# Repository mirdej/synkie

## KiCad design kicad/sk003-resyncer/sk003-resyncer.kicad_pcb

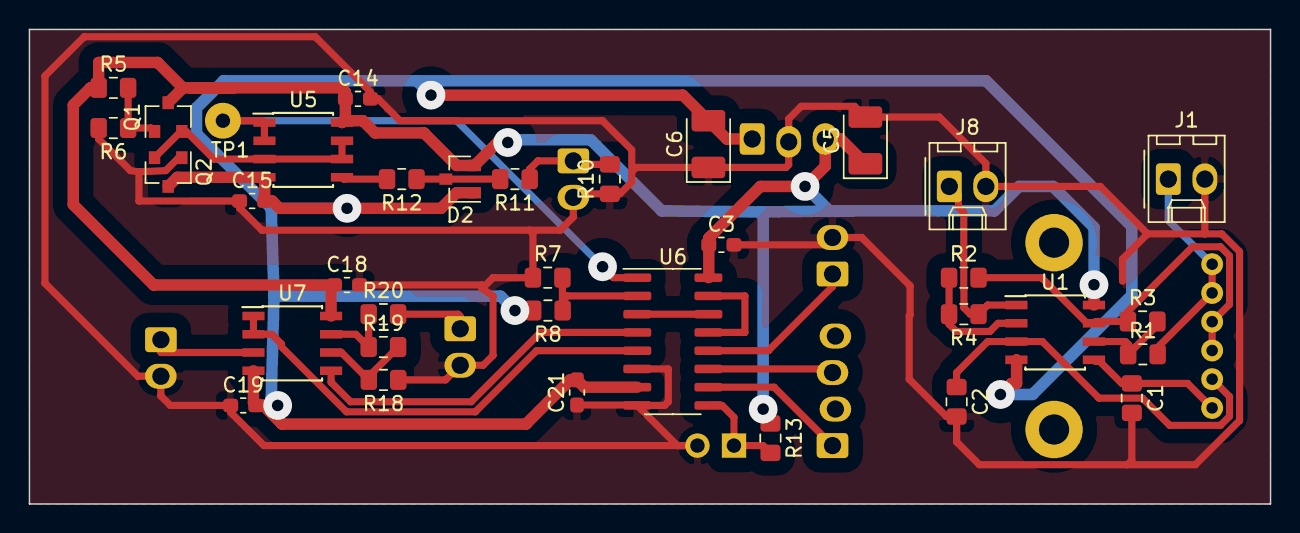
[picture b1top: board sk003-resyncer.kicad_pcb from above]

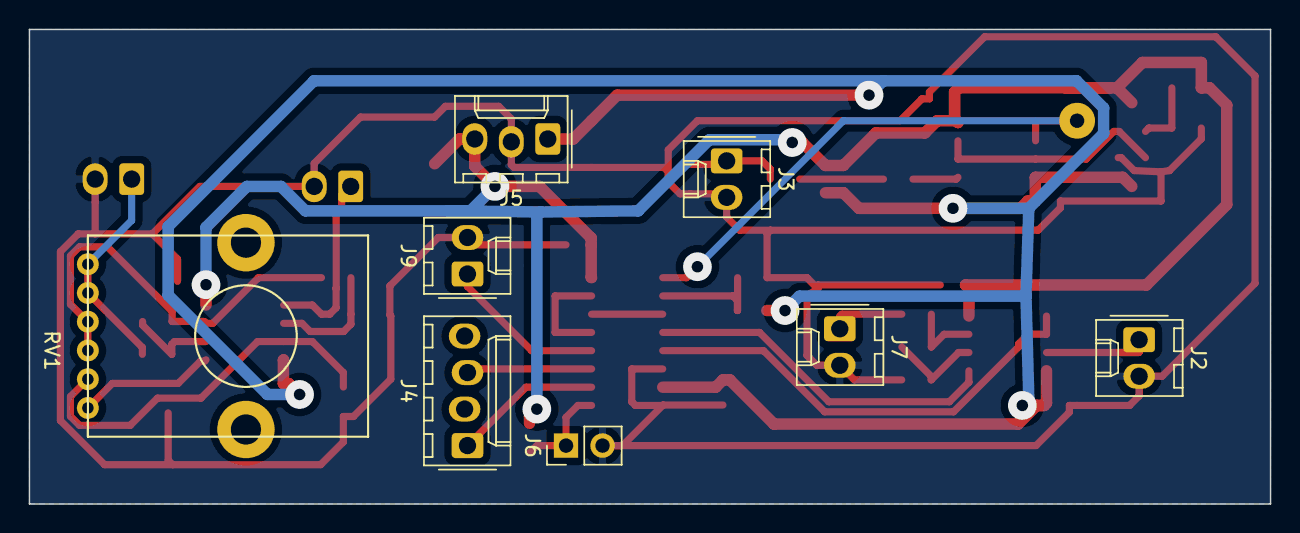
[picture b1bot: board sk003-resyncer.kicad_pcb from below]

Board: 2 copper layers, 86.4 x 33.0 mm, 43 parts (8 on the bottom side), 29 nets.

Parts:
C1, C2: 10p; C_0805_2012Metric_Pad1.15x1.40mm_HandSolder
C3, C14, C15, C18, C19, C21: 100n; C_0603_1608Metric_Pad1.05x0.95mm_HandSolder
C5, C6: 10u; CP_EIA-3528-21_Kemet-B_Pad1.50x2.35mm_HandSolder
D2: BAT54S; SOT-23
J1: BURST_IN; Molex_KK-254_AE-6410-02A_1x02_P2.54mm_Vertical
J2: GENLOCK; Molex_KK-254_AE-6410-02A_1x02_P2.54mm_Vertical
J3: SIFF_IN; Molex_KK-254_AE-6410-02A_1x02_P2.54mm_Vertical
J4: Conn_01x04; Molex_KK-254_AE-6410-04A_1x04_P2.54mm_Vertical
J5: Conn_01x03; Molex_KK-254_AE-6410-03A_1x03_P2.54mm_Vertical
J6: Switch; PinHeader_1x02_P2.54mm_Vertical
J7: VIDEO_OUT; Molex_KK-254_AE-6410-02A_1x02_P2.54mm_Vertical
J8: BURST_DELAYED; Molex_KK-254_AE-6410-02A_1x02_P2.54mm_Vertical
J9: Colorburst; Molex_KK-254_AE-6410-02A_1x02_P2.54mm_Vertical
Q1: Trans_NPN_Generic; SOT-23_BEC
Q2: Trans_PNP_Generic; SOT-23_BEC
R1, R2, R3, R4, R18, R19: 220; R_0805_2012Metric_Pad1.15x1.40mm_HandSolder
R5: 1k; R_0805_2012Metric_Pad1.15x1.40mm_HandSolder
R6: 150; R_0805_2012Metric_Pad1.15x1.40mm_HandSolder
R7: 300; R_0805_2012Metric_Pad1.15x1.40mm_HandSolder
R8, R13: 4k7; R_0805_2012Metric_Pad1.15x1.40mm_HandSolder
R10: 47k; R_0805_2012Metric_Pad1.15x1.40mm_HandSolder
R11, R12, R20: 75; R_0805_2012Metric_Pad1.15x1.40mm_HandSolder
RV1: R_POT_Dual; RK12L123
TP1: TestPoint; Solderpad_1mm
U1, U5, U7: LMH6643; SOIC-8_3.9x4.9mm_P1.27mm
U6: 4053; SOIC-16_3.9x9.9mm_P1.27mm

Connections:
+5V: C3.1, C5.1, C14.1, C18.1, D2.2, J5.3, Q1.C, R5.1, R13.1, U1.8, U5.8, U6.16, U7.8
-5V: C6.2, C15.2, C19.2, C21.2, D2.1, J5.1, Q2.C, R8.2, U1.4, U5.4, U6.7, U7.4
/clipper_out: TP1.1, U5.1, U5.2, U6.1
/colorburst: J9.1, U6.12
/hsync: J4.1, U6.10
/porch: J4.3, U6.11
/synctip: R7.2, R8.1, U6.2
GND: C1.2, C2.2, C3.2, C5.2, C6.1, C14.2, C15.1, C18.2, C19.1, C21.1, J1.2, J2.2, J3.2, J5.2, J6.2, J7.2, J8.2, J9.2, Q2.B, R6.2, R7.1, R10.1, R18.1, U6.6, U6.8
unnamed: C1.1, RV1.3, U1.5
unnamed: C2.1, RV1.6, U1.3
unnamed: D2.3, R11.2, R12.1
unnamed: J1.1, R1.2, RV1.1, RV1.2
unnamed: J2.1, U7.3
unnamed: J3.1, R10.2, R11.1
unnamed: J6.1, R13.2, U6.9
unnamed: J7.1, R20.2
unnamed: J8.1, R4.1, U1.1
unnamed: Q1.B, R5.2, R6.1
unnamed: Q1.E, Q2.E, U5.3, U5.6, U5.7
unnamed: R1.1, R3.2, U1.6
unnamed: R2.1, R4.2, U1.2
unnamed: R2.2, R3.1, RV1.4, RV1.5, U1.7
unnamed: R12.2, U5.5
unnamed: R18.2, R19.2, U7.6
unnamed: R19.1, R20.1, U7.7
unnamed: U6.4, U7.5
unnamed: U6.5, U7.1, U7.2
unnamed: U6.13, U6.15
unnamed: U6.3, U6.14

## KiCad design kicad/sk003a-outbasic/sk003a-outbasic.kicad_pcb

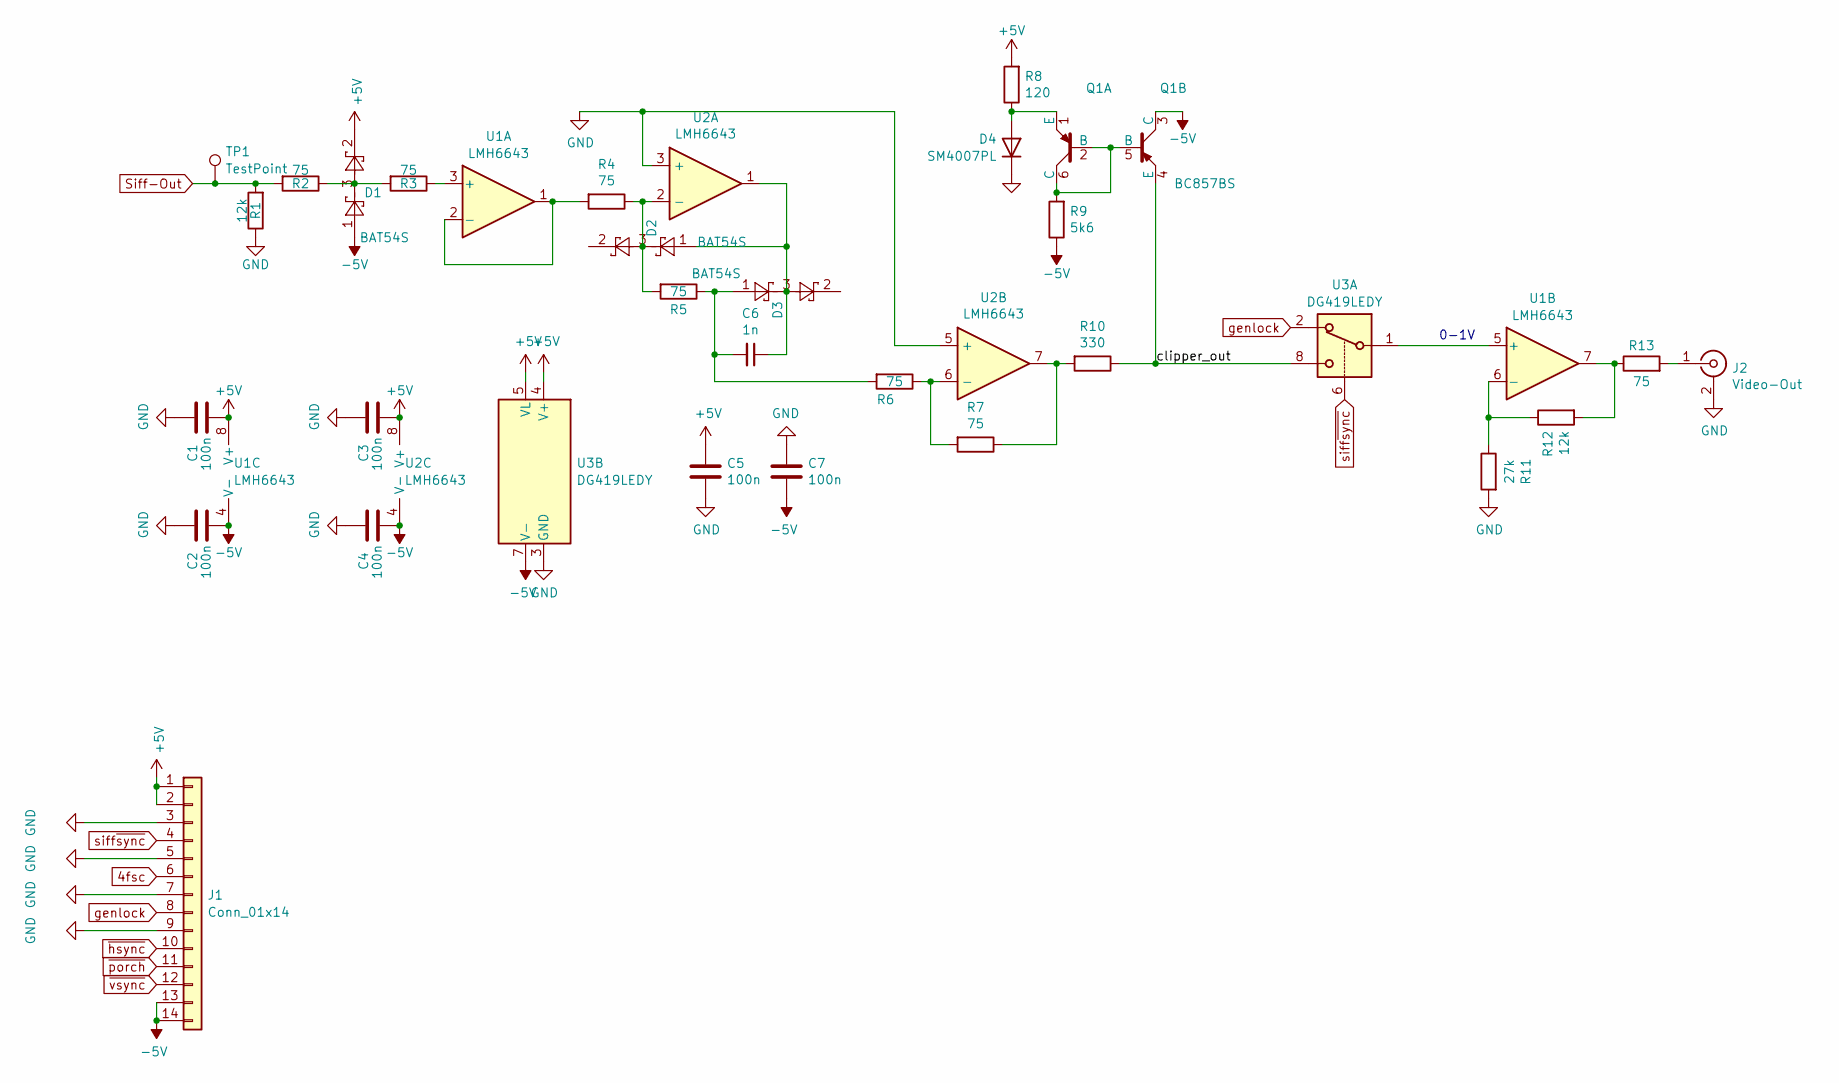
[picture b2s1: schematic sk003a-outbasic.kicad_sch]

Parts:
C1, C2, C3, C4, C5, C7: 100n; C_0603_1608Metric; LCSC C14663
C6: 1n; C_0603_1608Metric; LCSC C1588
D1, D2, D3: BAT54S; SOT-23; LCSC C7420333
D4: SM4007PL; D_SOD-123F; LCSC C64898
J1: Conn_01x14; SYNKIE-BUS.v3
J2: Video-Out; BNC_Aliexpress
Q1: BC857BS; SOT-363_SC-70-6_Handsoldering; LCSC C22381405
R1, R12: 12k; R_0603_1608Metric; LCSC C22790
R2, R3, R4, R5, R6, R7, R13: 75; R_0603_1608Metric; LCSC C4275
R8: 120; R_0603_1608Metric; LCSC C22787
R9: 5k6; R_0603_1608Metric; LCSC C23189
R10: 330; R_0603_1608Metric; LCSC C23138
R11: 27k; R_0603_1608Metric; LCSC C22967
TP1: TestPoint; TestPoint_THTPad_D4.0mm_Drill2.0mm
U1, U2: LMH6643; VSSOP-8_3x3mm_P0.65mm; LCSC C478382
U3: DG419LEDY; SOIC-8_3.9x4.9mm_P1.27mm; LCSC C2673265

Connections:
4fsc: J1.6
+5V: C1.2, C3.2, C5.1, D1.2, J1.1, J1.2, R8.2, U1.8 (V+), U2.8 (V+), U3.4 (V+), U3.5 (VL)
-5V: C2.2, C4.2, C7.2, D1.1, J1.13, J1.14, Q1.3 (C), R9.1, U1.4 (V-), U2.4 (V-), U3.7 (V-)
/clipper_out: Q1.4 (E), R10.1, U3.8
GND: C1.1, C2.1, C3.1, C4.1, C5.2, C7.1, D4.1 (K), J1.3, J1.5, J1.7, J1.9, J2.2 (Ext), R1.1, R11.2, U2.3 (+), U2.5 (+), U3.3 (GND)
unnamed: C6.1, D2.1, D3.3, U2.1
unnamed: C6.2, D3.1, R5.1, R6.2
unnamed: D1.3, R2.1, R3.2
unnamed: D4.2 (A), Q1.1 (E), R8.1
unnamed: J2.1 (In), R13.2
unnamed: Q1.2 (B), Q1.5 (B), Q1.6 (C), R9.2
unnamed: R7.1, R10.2, U2.7
unnamed: R12.2, R13.1, U1.7
unnamed: R3.1, U1.3 (+)
unnamed: R4.2, U1.1, U1.2 (-)
unnamed: U1.5 (+), U3.1
unnamed: R11.1, R12.1, U1.6 (-)
unnamed: D2.3, R4.1, R5.2, U2.2 (-)
unnamed: R6.1, R7.2, U2.6 (-)
Siff-Out: R1.2, R2.2, TP1.1 (1_1)
genlock: J1.8, U3.2
siff~sync: J1.4, U3.6
~hsync: J1.10
~porch: J1.11
~vsync: J1.12

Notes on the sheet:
0-1V

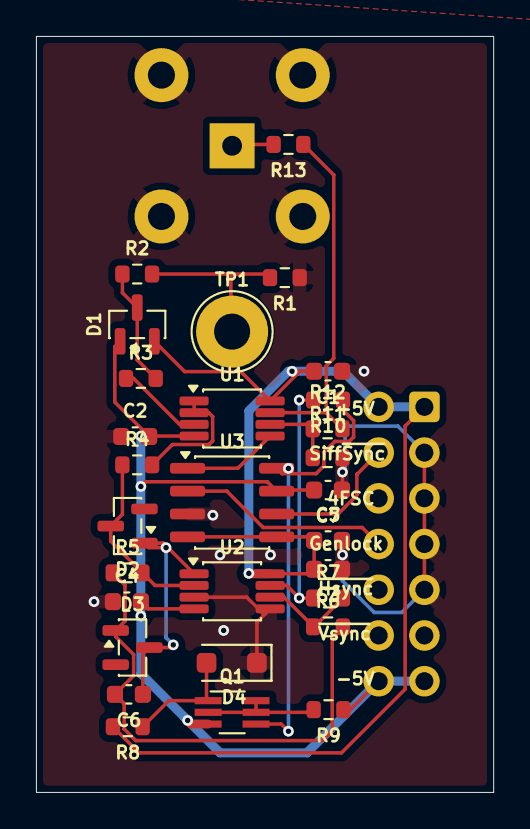
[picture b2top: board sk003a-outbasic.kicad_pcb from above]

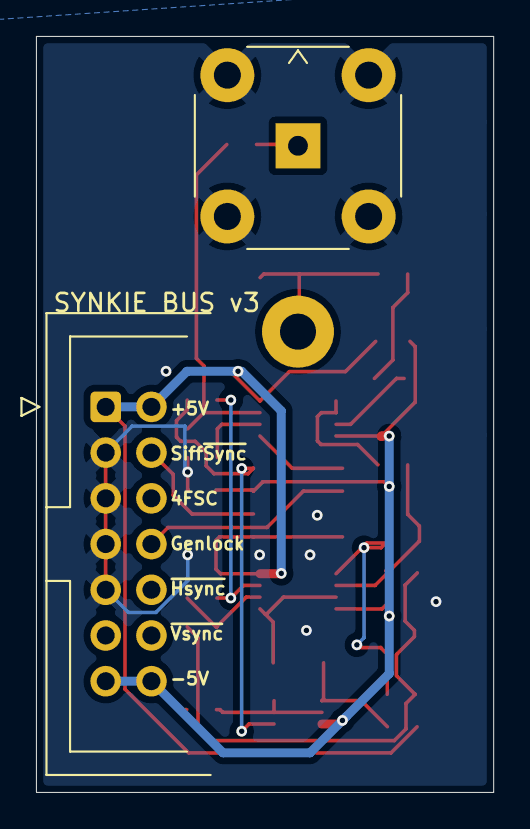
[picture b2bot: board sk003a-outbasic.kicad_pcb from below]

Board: 2 copper layers, 25.4 x 42.0 mm, 31 parts (2 on the bottom side), 21 nets.

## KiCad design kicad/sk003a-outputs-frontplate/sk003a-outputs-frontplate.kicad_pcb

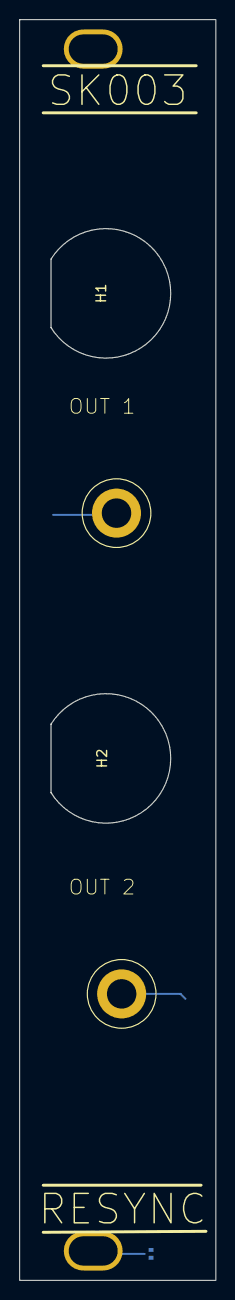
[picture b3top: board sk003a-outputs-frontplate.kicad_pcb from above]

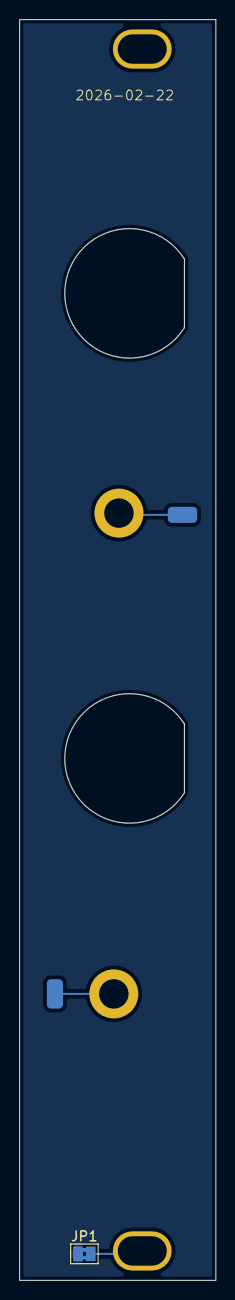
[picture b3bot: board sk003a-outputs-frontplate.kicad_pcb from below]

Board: 2 copper layers, 20.0 x 128.5 mm, 8 parts (3 on the bottom side), 3 nets.

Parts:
H1, H2: BNC; MolexBNCFrontpanel
J6: Out1; Banana2mm-Löthülse
J7: OUT; Banana2mm-Löthülse
J8, J9: Conn_01x01_Socket; smd-1pin
JP1: Jumper_2_Bridged; SolderJumper-2_P1.3mm_Bridged2Bar_Pad1.0x1.5mm
N1: Housing; Frontplate_20mm

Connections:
unnamed: J6.1 (Pin_1_1), J9.1 (Pin_1_1)
unnamed: J7.1 (Pin_1_1), J8.1 (Pin_1_1)
unnamed: JP1.2 (B), N1.1 (PAD_1)

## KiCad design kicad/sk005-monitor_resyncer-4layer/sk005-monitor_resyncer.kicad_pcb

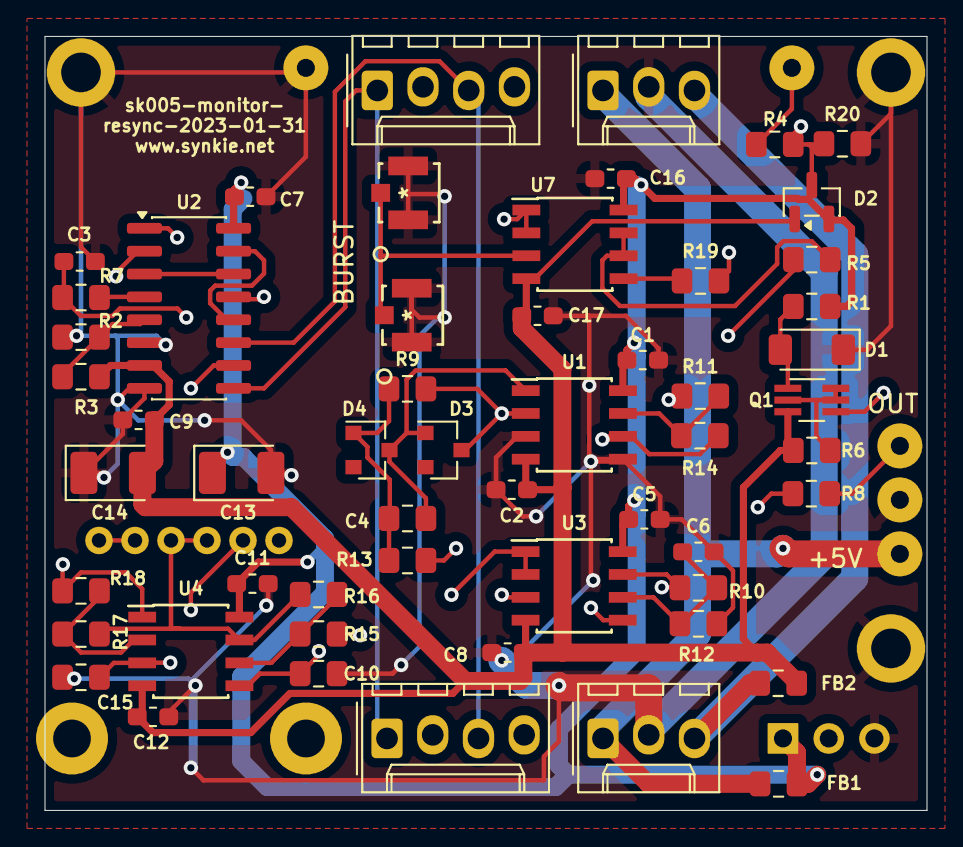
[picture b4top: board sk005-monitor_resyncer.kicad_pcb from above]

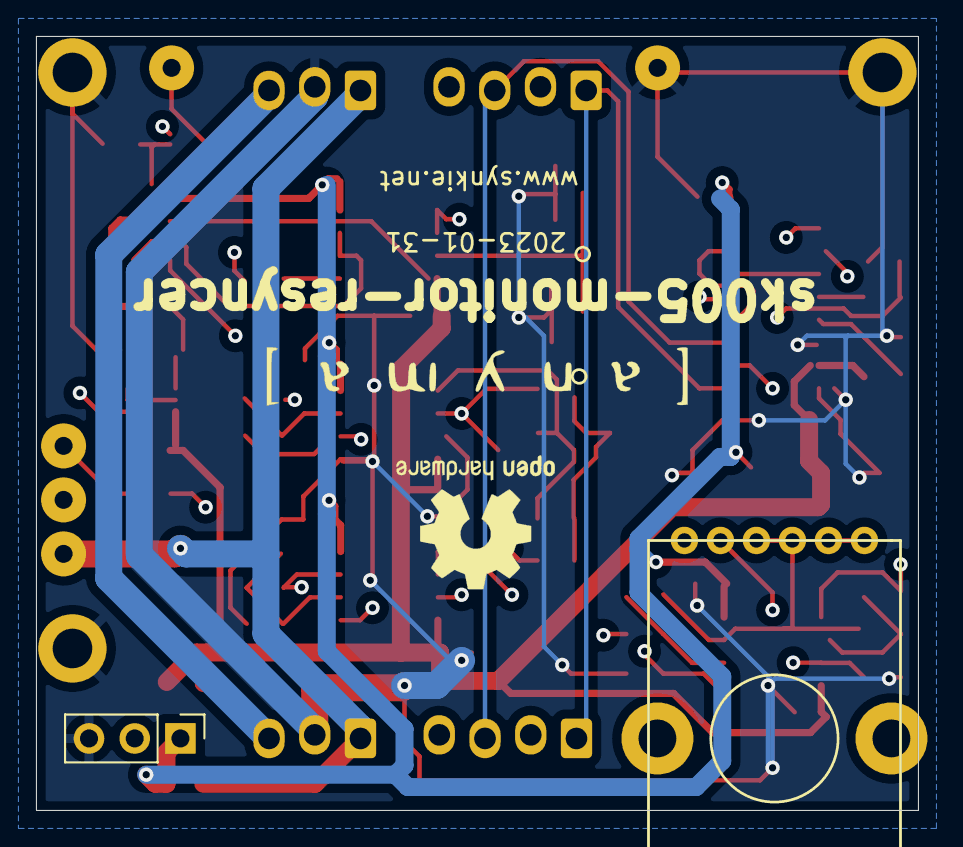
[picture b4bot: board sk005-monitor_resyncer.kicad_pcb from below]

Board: 4 copper layers, 49.0 x 43.0 mm, 67 parts (4 on the bottom side), 37 nets.

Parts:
C1, C2, C5, C7, C8, C9, C11, C12, C16, C17: 100n; C_0603_1608Metric_Pad1.05x0.95mm_HandSolder
C3: 120p; C_0603_1608Metric_Pad1.05x0.95mm_HandSolder
C4: 1n; C_0805_2012Metric_Pad1.15x1.40mm_HandSolder
C6: 10p; C_0603_1608Metric_Pad1.05x0.95mm_HandSolder
C10, C15: 10p; C_0805_2012Metric_Pad1.15x1.40mm_HandSolder
C13, C14: 10u; CP_EIA-3528-21_Kemet-B_Pad1.50x2.35mm_HandSolder
D1: D; D_MiniMELF
D2: BAT54S; SOT-23
D3, D4: BAT54; D_SOT-23_ANK
FB1, FB2: 330u; L_0805_2012Metric_Pad1.15x1.40mm_HandSolder
H1, H2, H3: MountingHole_Pad; MountingHole_2.2mm_M2_DIN965_Pad
J1: IN; Solderpad_1mm
J2: OUT; Solderpad_1mm
J3: 5V; Solderpad_1mm
J4: Burst-Thru; TE_UMCC_2337019-1
J5, J8: gnd; Solderpad_1mm
J6, J10: SYNC; Molex_KK-254_AE-6410-04A_1x04_P2.54mm_Vertical
J7, J11: Power; Molex_KK-254_AE-6410-03A_1x03_P2.54mm_Vertical
J9: Delayed_burst_in; TE_UMCC_2337019-1
Q1: PMBT3906YS; SOT-363_SC-70-6_Handsoldering
R1, R7: 120; R_0805_2012Metric_Pad1.15x1.40mm_HandSolder
R2: 300; R_0805_2012Metric_Pad1.15x1.40mm_HandSolder
R3: 4k7; R_0805_2012Metric_Pad1.15x1.40mm_HandSolder
R4: 12k; R_0805_2012Metric_Pad1.15x1.40mm_HandSolder
R5, R8, R9, R13, R14, R19: 75; R_0805_2012Metric_Pad1.15x1.40mm_HandSolder
R6: 5k6; R_0805_2012Metric_Pad1.15x1.40mm_HandSolder
R10, R12, R15, R16, R17, R18: 220; R_0805_2012Metric_Pad1.15x1.40mm_HandSolder
R11: 330; R_0805_2012Metric_Pad1.15x1.40mm_HandSolder
R20: 30k; R_0805_2012Metric_Pad1.15x1.40mm_HandSolder
RV1: R_POT_Dual; RK12L123
SW1: SW_SPDT; PinHeader_1x03_P2.54mm_Vertical
U1, U3, U7: LMH6643; SOIC-8_3.9x4.9mm_P1.27mm
U2: 4053; SOIC-16_3.9x9.9mm_P1.27mm
U4: Opamp_Dual_Generic; SOIC-8_3.9x4.9mm_P1.27mm
U5: LOGO; logo_anyma
U6: LOGO; OSHW-Logo2_9.8x8mm_SilkScreen

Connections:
+5V: C1.2, C5.2, C7.2, C11.1, C13.1, C16.2, D2.2, FB1.2, R1.2, SW1.1 (A), U1.8 (V+), U2.16 (VDD), U3.8 (V+), U4.8 (V+), U7.8 (V+)
-5V: C2.1, C8.1, C9.1, C12.1, C14.2, C17.1, D2.1, FB2.2, Q1.3 (C), R3.2, R6.1, U1.4 (V-), U2.7 (VEE), U3.4 (V-), U4.4 (V-), U7.4 (V-)
/burst_select: SW1.2 (B), U2.10 (B)
/clipper_out: U2.13 (X1), U3.1, U3.2 (-)
/local_delayed_burst: R18.1, U2.2 (Y0), U4.1
/pre_delayed_burst: R15.2, RV1.1, RV1.2, U2.1 (Y1), U7.1, U7.2 (-)
/supply+: FB1.1, J3.1, J7.1, J11.1
/supply-: FB2.1, J7.3, J11.3
/synctip: R2.2, R3.1, U2.5 (Z0)
GND: C1.1, C2.2, C3.2, C5.1, C6.2, C7.1, C8.2, C9.2, C10.2, C11.2, C12.2, C13.2, C14.1, C15.2, C16.1, C17.2, D1.1 (K), H1.1, H2.1, H3.1, J4.2, J4.3, J5.1, J7.2, J8.1, J9.2, J9.3, J11.2, R2.1, R12.1, R20.2, SW1.3 (C), U1.3 (+), U1.5 (+), U2.6 (Inh), U2.8 (VSS)
unnamed: C3.1, R7.1, U3.5 (+)
unnamed: C4.1, D3.2 (A), D4.1 (K), U1.1
unnamed: C4.2, D4.2 (A), R9.1, R13.2
unnamed: C6.1, R10.2, R12.2, U3.6 (-)
unnamed: C10.1, RV1.3, U4.5 (+)
unnamed: C15.1, RV1.6, U4.3 (+)
unnamed: D1.2 (A), Q1.1 (E), R1.1
unnamed: D2.3, R4.1, R19.2, R20.1
unnamed: D3.1 (K), R5.1, R9.2, U1.2 (-)
unnamed: J1.1, R4.2
unnamed: J2.1, R8.2
unnamed: J4.1, J9.1, U7.3 (+)
unnamed: Q1.2 (B), Q1.5 (B), Q1.6 (C), R6.2
unnamed: Q1.4 (E), R11.1, U3.3 (+)
unnamed: R5.2, U7.6 (-), U7.7
unnamed: R7.2, U2.4 (Z)
unnamed: R8.1, R10.1, U3.7
unnamed: R11.2, R14.1, U1.7
unnamed: R13.1, R14.2, U1.6 (-)
unnamed: R15.1, R16.2, U4.6 (-)
unnamed: R16.1, R17.2, RV1.4, RV1.5, U4.7
unnamed: R17.1, R18.2, U4.2 (-)
unnamed: R19.1, U7.5 (+)
unnamed: U2.12 (X0), U2.15 (Y)
unnamed: U2.3 (Z1), U2.14 (X)
hsync: J6.1, J10.1, U2.9 (C)
porch: J6.3, J10.3, U2.11 (A)

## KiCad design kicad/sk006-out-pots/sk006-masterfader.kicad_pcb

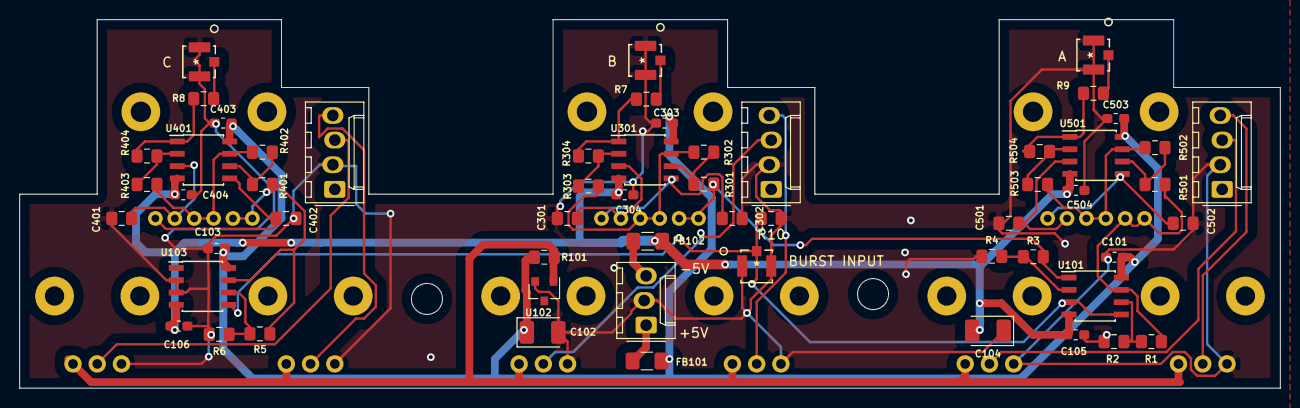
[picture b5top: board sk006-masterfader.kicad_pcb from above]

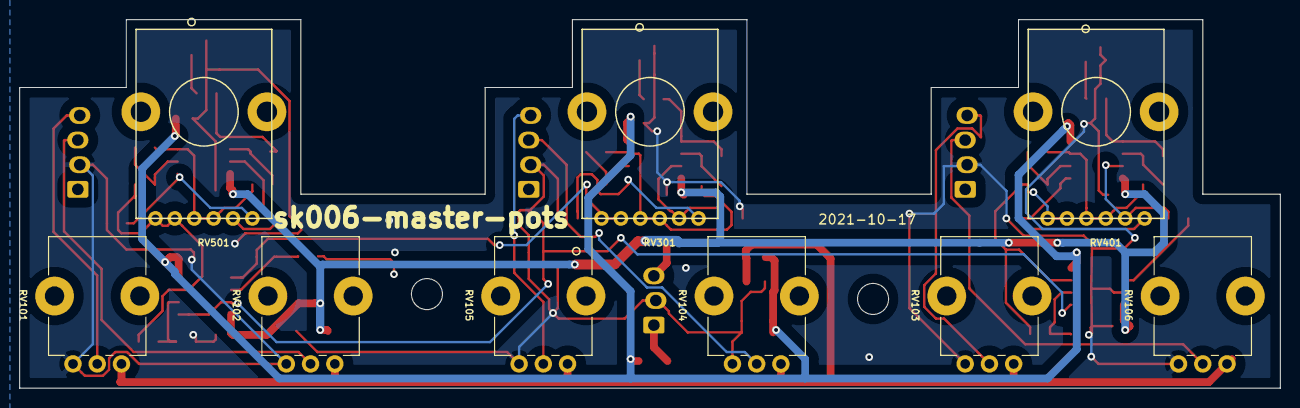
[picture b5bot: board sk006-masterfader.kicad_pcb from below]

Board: 2 copper layers, 130.0 x 38.0 mm, 68 parts (9 on the bottom side), 40 nets.

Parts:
C101, C103, C105, C106, C303, C304, C403, C404, C503, C504: 100n; C_0603_1608Metric_Pad1.05x0.95mm_HandSolder
C102, C104: CP; CP_EIA-3528-21_Kemet-B_Pad1.50x2.35mm_HandSolder
C301, C302, C401, C402, C501, C502: 10p; C_0805_2012Metric_Pad1.15x1.40mm_HandSolder
FB101, FB102: Ferrite_Bead; L_1206_3216Metric_Pad1.42x1.75mm_HandSolder
H1, H2: MountingHole; MountingHole_3.2mm_M3
J1, J201, J301, J401: UMCC; TE_UMCC_2337019-1
J101: Conn_01x03; Molex_KK-254_AE-6410-03A_1x03_P2.54mm_Vertical
J103: A; Molex_KK-254_AE-6410-04A_1x04_P2.54mm_Vertical
J104: B; Molex_KK-254_AE-6410-04A_1x04_P2.54mm_Vertical
J105: C; Molex_KK-254_AE-6410-04A_1x04_P2.54mm_Vertical
R1, R2, R3, R4, R5, R6, R301, R302, R303, R304, R401, R402, R403, R404, R501, R502, R503, R504: 220; R_0805_2012Metric_Pad1.15x1.40mm_HandSolder
R7, R8, R9, R10: 75; R_0805_2012Metric_Pad1.15x1.40mm_HandSolder
R101: 560; R_0805_2012Metric_Pad1.15x1.40mm_HandSolder
RV101, RV103, RV105: SCALE; Potentiometer_Alps_RK09K_Single_Vertical
RV102, RV104, RV106: BIAS; Potentiometer_Alps_RK09K_Single_Vertical
RV301, RV401, RV501: R_POT_Dual; RK12L123
U101, U103, U301, U401, U501: LMH6643; SOIC-8_3.9x4.9mm_P1.27mm
U102: ADR510; SOT-23

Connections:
+5V: C101.1, C102.1, C103.1, C303.2, C403.2, C503.2, FB101.1, R101.1, U101.8, U103.8, U301.8, U401.8, U501.8
-5V: C104.2, C105.1, C106.1, C304.1, C404.1, C504.1, FB102.1, U101.4, U103.4, U301.4, U401.4, U501.4
/Phase1/INPUT: R1.2, R501.2, RV501.1, RV501.2, U101.7
/Phase1/OUTPUT: R9.2, R504.1, U501.1
/sheet5FF0F8E5/INPUT: R5.2, R401.2, RV401.1, RV401.2, U103.7
/sheet5FF0F8E5/OUTPUT: R8.2, R404.1, U401.1
/sheet5FF0F40B/INPUT: R3.2, R301.2, RV301.1, RV301.2, U101.1
/sheet5FF0F40B/OUTPUT: R7.2, R304.1, U301.1
GND: C101.2, C102.2, C103.2, C104.1, C105.2, C106.2, C301.2, C302.2, C303.1, C304.2, C401.2, C402.2, C403.1, C404.2, C501.2, C502.2, C503.1, C504.2, J1.2, J1.3, J101.2, J103.2, J104.2, J105.2, J201.2, J201.3, J301.2, J301.3, J401.2, J401.3, R2.1, R4.1, R6.1, R10.1, RV101.3, RV102.3, RV103.3, RV104.3, RV105.3, RV106.3, U102.2, U103.2, U103.3
unnamed: C301.1, RV301.6, U301.3
unnamed: C302.1, RV301.3, U301.5
unnamed: C401.1, RV401.6, U401.3
unnamed: C402.1, RV401.3, U401.5
unnamed: C501.1, RV501.6, U501.3
unnamed: C502.1, RV501.3, U501.5
unnamed: FB101.2, J101.1
unnamed: FB102.2, J101.3
unnamed: J1.1, R10.2, U101.3, U101.5, U103.5
unnamed: J103.3, RV102.2
unnamed: J103.4, RV101.2
unnamed: J104.3, RV104.2
unnamed: J104.4, RV105.2
unnamed: J105.3, RV106.2
unnamed: J105.4, RV103.2
unnamed: J201.1, R9.1
unnamed: J301.1, R7.1
unnamed: J401.1, R8.1
unnamed: R1.1, R2.2, U101.6
unnamed: R3.1, R4.2, U101.2
unnamed: R5.1, R6.2, U103.6
unnamed: R301.1, R302.2, U301.6
unnamed: R302.1, R303.2, RV301.4, RV301.5, U301.7
unnamed: R303.1, R304.2, U301.2
unnamed: R401.1, R402.2, U401.6
unnamed: R402.1, R403.2, RV401.4, RV401.5, U401.7
unnamed: R403.1, R404.2, U401.2
unnamed: R501.1, R502.2, U501.6
unnamed: R502.1, R503.2, RV501.4, RV501.5, U501.7
unnamed: R503.1, R504.2, U501.2
VCCQ: R101.2, RV101.1, RV102.1, RV103.1, RV104.1, RV105.1, RV106.1, U102.1

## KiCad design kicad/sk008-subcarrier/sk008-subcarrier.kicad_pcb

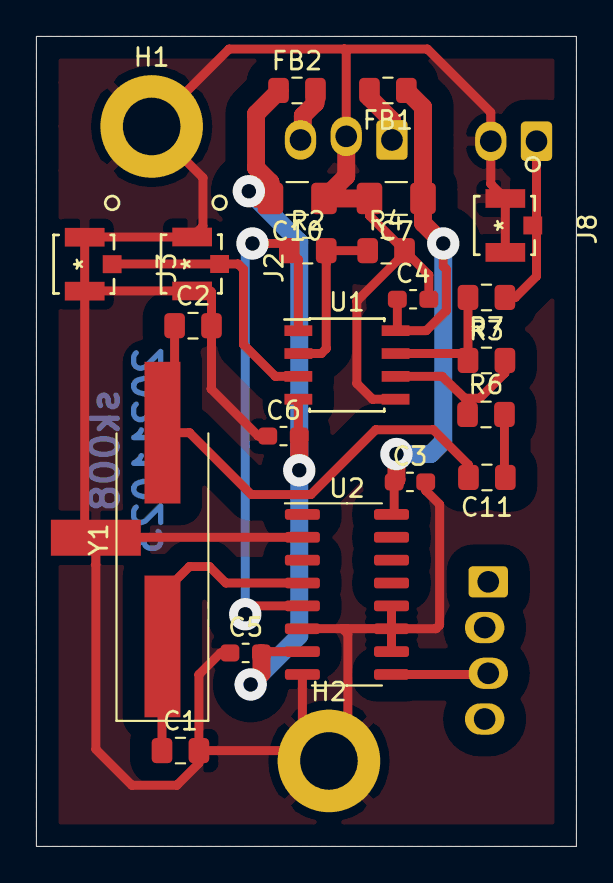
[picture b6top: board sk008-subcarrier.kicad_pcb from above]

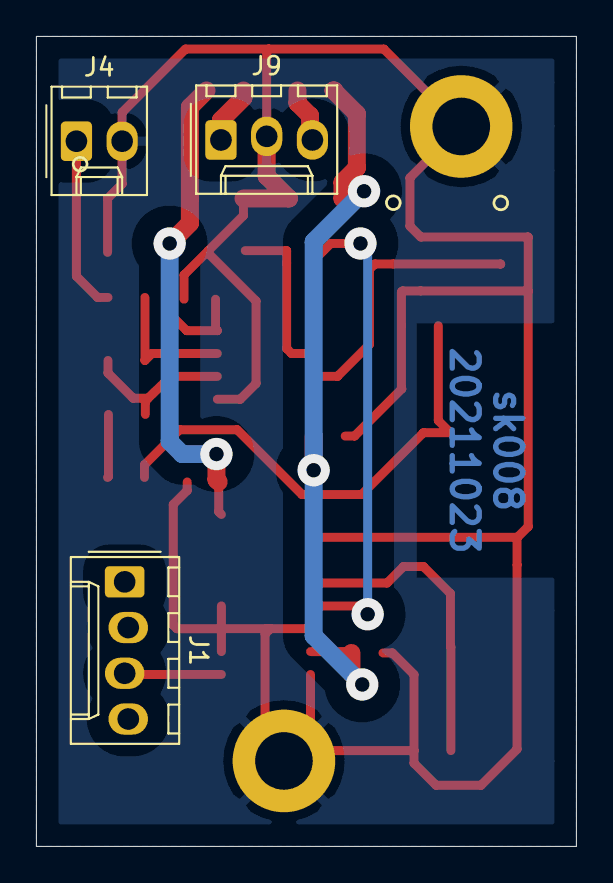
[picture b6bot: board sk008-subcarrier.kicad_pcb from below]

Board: 2 copper layers, 30.0 x 45.0 mm, 27 parts (3 on the bottom side), 15 nets.

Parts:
C1, C2: 22p; C_0805_2012Metric_Pad1.15x1.40mm_HandSolder
C3, C4, C5, C6: 100n; C_0603_1608Metric_Pad1.05x0.95mm_HandSolder
C7, C10: 10u; C_1206_3216Metric_Pad1.42x1.75mm_HandSolder
C11: 100n; C_0805_2012Metric_Pad1.15x1.40mm_HandSolder
FB1, FB2: Ferrite_Bead; L_0805_2012Metric_Pad1.15x1.40mm_HandSolder
H1, H2: MountingHole_Pad; MountingHole_3.2mm_M3_ISO7380_Pad
J1: Conn_01x04; Molex_KK-254_AE-6410-04A_1x04_P2.54mm_Vertical
J2: Burst in; TE_UMCC_2337019-1
J3: Burst through; TE_UMCC_2337019-1
J4: subcarrier-out; Molex_KK-254_AE-6410-02A_1x02_P2.54mm_Vertical
J8: subcarrier-out; TE_UMCC_2337019-1
J9: Conn_01x03; Molex_KK-254_AE-6410-03A_1x03_P2.54mm_Vertical
R2: 2k; R_0805_2012Metric_Pad1.15x1.40mm_HandSolder
R3: 100k; R_0805_2012Metric_Pad1.15x1.40mm_HandSolder
R4: 560; R_0805_2012Metric_Pad1.15x1.40mm_HandSolder
R6: 10k; R_0805_2012Metric_Pad1.15x1.40mm_HandSolder
R7: 75; R_0805_2012Metric_Pad1.15x1.40mm_HandSolder
U1: LMH6643; SOIC-8_3.9x4.9mm_P1.27mm
U2: 4053; SOIC-16_3.9x9.9mm_P1.27mm
Y1: Crystal_GND2; Crystal_SMD_HC49-SD_HandSoldering_3pin

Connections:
+5V: C3.1, C4.1, C7.1, FB1.1, U1.8, U2.16
-5V: C5.2, C6.2, C10.2, FB2.1, U1.4, U2.7
/burstin: J2.1, J3.1, U1.3
/porch: J1.3, U2.9
GND: C1.2, C2.2, C3.2, C4.2, C5.1, C6.1, C7.2, C10.1, H1.1, H2.1, J2.2, J2.3, J3.2, J3.3, J4.2, J8.2, J8.3, J9.2, R4.2, U1.5, U2.2, U2.6, U2.8, U2.10, U2.11, U2.12, Y1.2
unnamed: C1.1, U2.4, Y1.1
unnamed: C11.1, R6.2
unnamed: C2.1, C11.2, Y1.3
unnamed: FB1.2, J9.1
unnamed: FB2.2, J9.3
unnamed: J4.1, J8.1, R7.1
unnamed: R2.1, U1.1, U2.5
unnamed: R2.2, R4.1, U1.2
unnamed: R3.1, R7.2, U1.7
unnamed: R3.2, R6.1, U1.6

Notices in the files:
parts and their libraries:
Copyright 2016 Accelerated Designs. All rights reserved.
